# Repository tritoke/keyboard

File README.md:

# keyboard

This is my efforts towards making the exact keyboard entirely for fun.

Wants:
- Usable over USB or Bluetooth
- 65% with arrow keys, ISO enter and the four keys on the right

Progress:
- PCB (rev1 done)
- Case (freeCAD is kicking my ass)
- Firmware (I have some thoughts and that is all)

## PCB

Revision 1 of the PCB is now complete:

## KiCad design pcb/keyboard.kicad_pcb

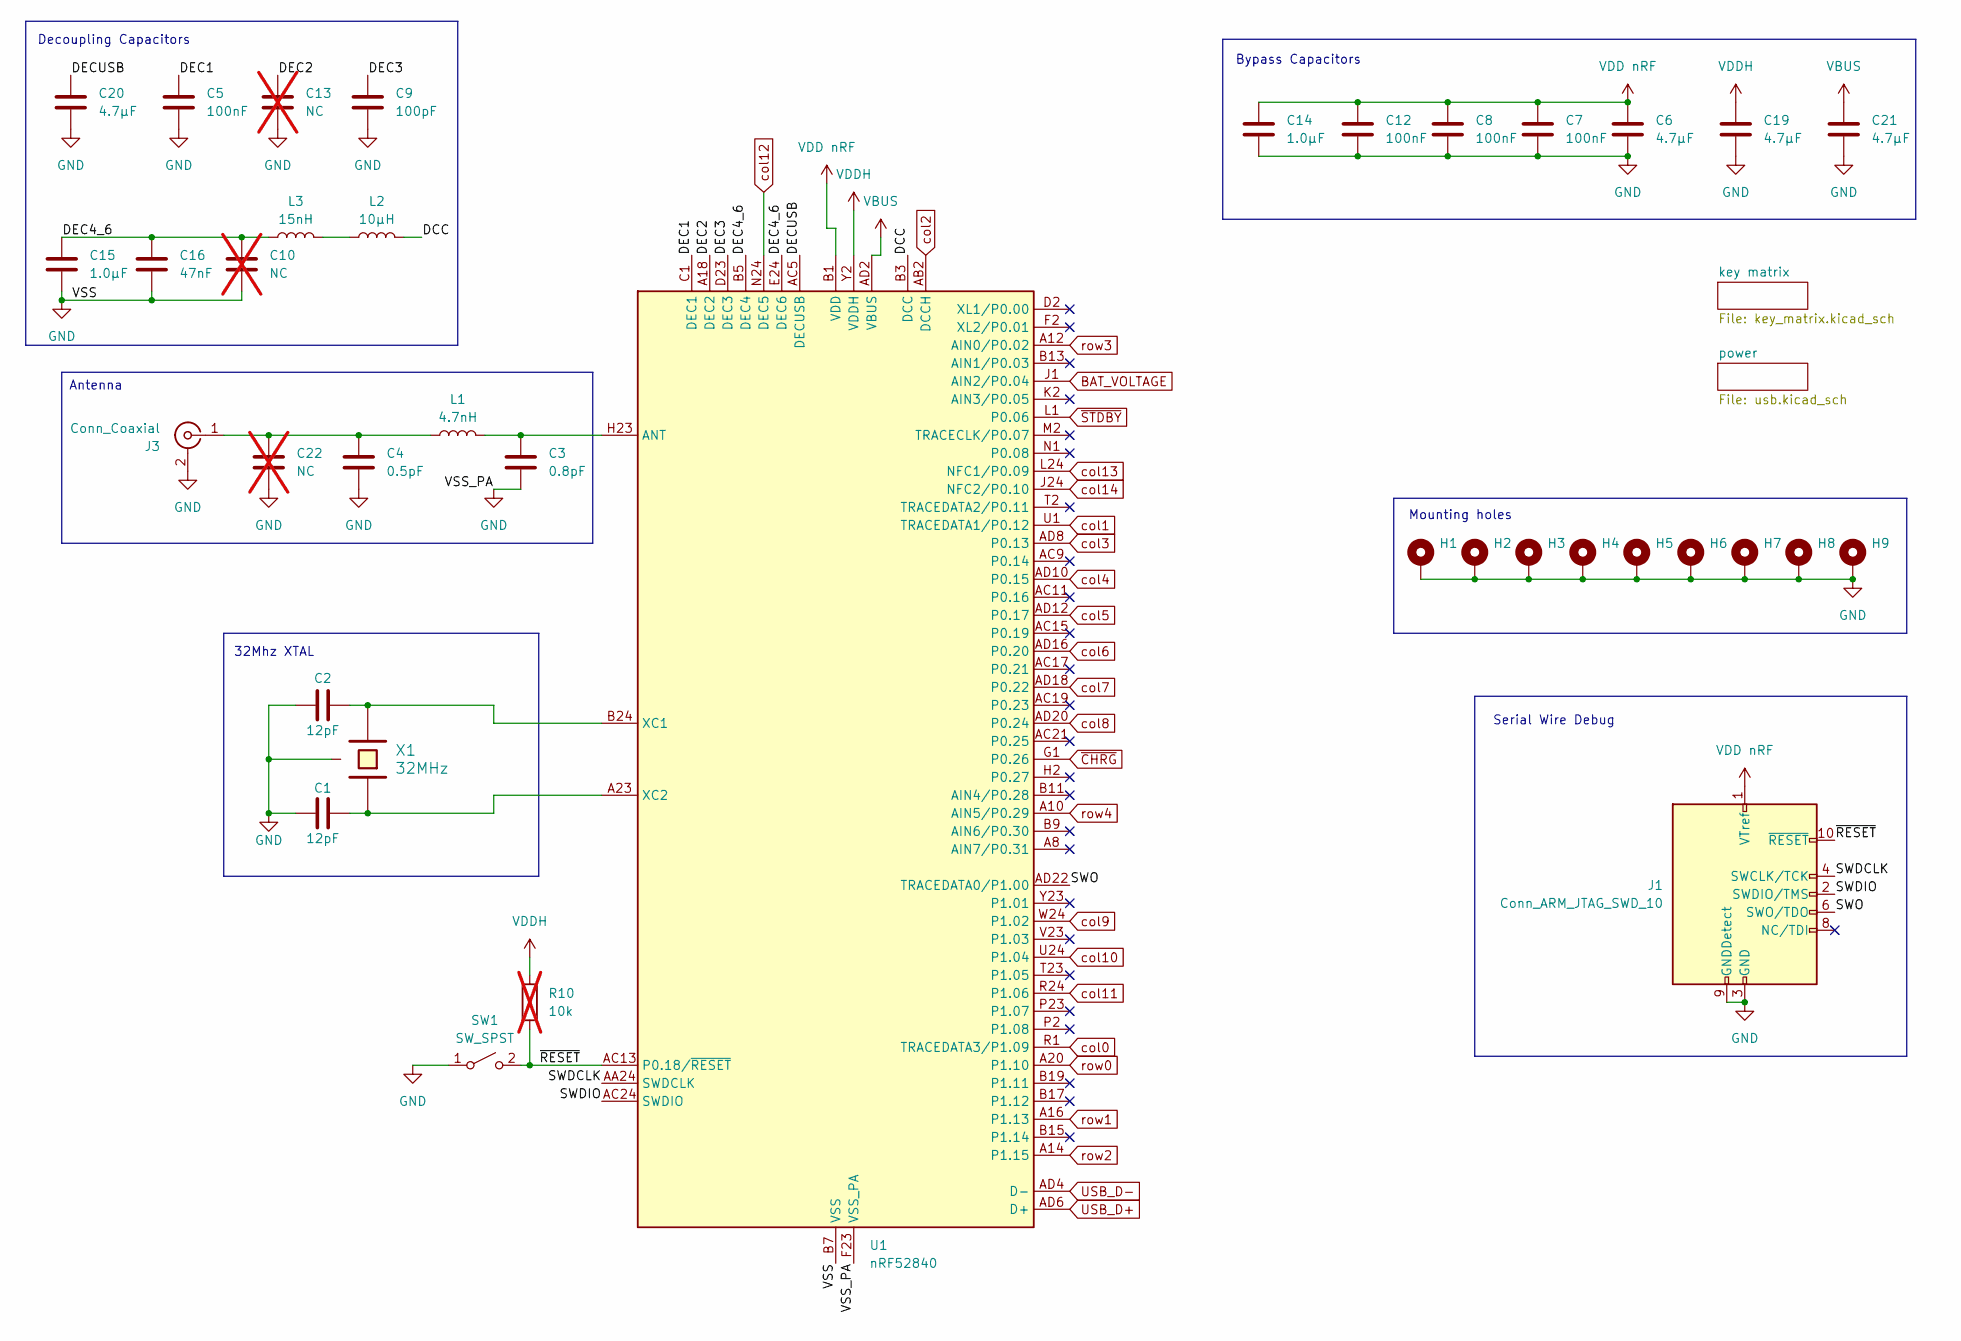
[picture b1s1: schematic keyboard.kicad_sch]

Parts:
C1, C2: 12pF; C_0603_1608Metric_Pad1.08x0.95mm_HandSolder
C3: 0.8pF; C_0603_1608Metric_Pad1.08x0.95mm_HandSolder
C4: 0.5pF; C_0603_1608Metric_Pad1.08x0.95mm_HandSolder
C5, C7, C8, C12: 100nF; C_0603_1608Metric_Pad1.08x0.95mm_HandSolder
C6, C19, C20, C21: 4.7µF; C_0603_1608Metric_Pad1.08x0.95mm_HandSolder
C9: 100pF; C_0603_1608Metric_Pad1.08x0.95mm_HandSolder
C10, C13, C22: NC; C_0603_1608Metric_Pad1.08x0.95mm_HandSolder; not fitted
C14, C15: 1.0µF; C_0603_1608Metric_Pad1.08x0.95mm_HandSolder
C16: 47nF; C_0603_1608Metric_Pad1.08x0.95mm_HandSolder
H1, H2, H3, H4, H5, H6, H7, H8, H9: MountingHole_Pad; MountingHole_2.2mm_M2_Pad_Via
J1: Conn_ARM_JTAG_SWD_10; IDC-Header_2x05_P2.54mm_Vertical
J3: Conn_Coaxial; SMA_Molex_73251-1153_EdgeMount_Horizontal_HandSolder
L1: 4.7nH; L_0603_1608Metric_Pad1.05x0.95mm_HandSolder
L2: 10µH; L_0603_1608Metric_Pad1.05x0.95mm_HandSolder
L3: 15nH; L_0603_1608Metric_Pad1.05x0.95mm_HandSolder
R10: 10k; R_0603_1608Metric_Pad0.98x0.95mm_HandSolder; not fitted
SW1: SW_SPST; Legion SS11
U1: nRF52840; Nordic_AQFN-73-1EP_7x7mm_P0.5mm
X1: 32MHz; Crystal_SMD_2016-4Pin_2.0x1.6mm_HandSolder

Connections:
/DCC: L2.2, U1.B3 (DCC)
/DEC1: C5.1, U1.C1 (DEC1)
/DEC2: C13.1, U1.A18 (DEC2)
/DEC3: C9.1, U1.D23 (DEC3)
/DEC4_6: C10.1, C15.1, C16.1, L3.1, U1.B5 (DEC4), U1.E24 (DEC6)
/DECUSB: C20.1, U1.AC5 (DECUSB)
/SWDCLK: J1.4 (SWCLK/TCK), U1.AA24 (SWDCLK)
/SWDIO: J1.2 (SWDIO/TMS), U1.AC24 (SWDIO)
/SWO: J1.6 (SWO/TDO), U1.AD22 (TRACEDATA0/P1.00)
/~RESET: J1.10 (~RESET), R10.2, SW1.2 (B), U1.AC13 (P0.18/~RESET)
BAT_VOLTAGE: U1.J1 (AIN2/P0.04); also elsewhere on the board
GND: C1.1, C2.1, C3.2, C4.2, C5.2, C6.2, C7.2, C8.2, C9.2, C10.2, C12.2, C13.2, C14.2, C15.2, C16.2, C19.2, C20.2, C21.2, C22.2, H1.1 (1_1), H2.1 (1_1), H3.1 (1_1), H4.1 (1_1), H5.1 (1_1), H6.1 (1_1), H7.1 (1_1), H8.1 (1_1), H9.1 (1_1), J1.3 (GND), J1.5 (GND), J1.9 (GNDDetect), J3.2 (Ext), SW1.1 (A), U1.B7 (VSS), U1.EP (VSS), U1.F23 (VSS_PA), X1.3; also elsewhere on the board
unnamed: C4.1, C22.1, J3.1 (In), L1.1
unnamed: L2.1, L3.2
unnamed: C3.1, L1.2, U1.H23 (ANT)
unnamed: C2.2, U1.B24 (XC1), X1.2
unnamed: C1.2, U1.A23 (XC2), X1.1
USB_D+: U1.AD6 (D+); also elsewhere on the board
USB_D-: U1.AD4 (D-); also elsewhere on the board
VBUS: C21.1, U1.AD2 (VBUS); also elsewhere on the board
VDD nRF: C6.1, C7.1, C8.1, C12.1, C14.1, J1.1 (VTref), U1.A22 (VDD), U1.AD14 (VDD), U1.AD23 (VDD), U1.B1 (VDD), U1.W1 (VDD)
VDDH: C19.1, R10.1, U1.Y2 (VDDH); also elsewhere on the board
col0: U1.R1 (TRACEDATA3/P1.09); also elsewhere on the board
col1: U1.U1 (TRACEDATA1/P0.12); also elsewhere on the board
col2: U1.AB2 (DCCH); also elsewhere on the board
col3: U1.AD8 (P0.13); also elsewhere on the board
col4: U1.AD10 (P0.15); also elsewhere on the board
col5: U1.AD12 (P0.17); also elsewhere on the board
col6: U1.AD16 (P0.20); also elsewhere on the board
col7: U1.AD18 (P0.22); also elsewhere on the board
col8: U1.AD20 (P0.24); also elsewhere on the board
col9: U1.W24 (P1.02); also elsewhere on the board
col10: U1.U24 (P1.04); also elsewhere on the board
col11: U1.R24 (P1.06); also elsewhere on the board
col12: U1.N24 (DEC5); also elsewhere on the board
col13: U1.L24 (NFC1/P0.09); also elsewhere on the board
col14: U1.J24 (NFC2/P0.10); also elsewhere on the board
row0: U1.A20 (P1.10); also elsewhere on the board
row1: U1.A16 (P1.13); also elsewhere on the board
row2: U1.A14 (P1.15); also elsewhere on the board
row3: U1.A12 (AIN0/P0.02); also elsewhere on the board
row4: U1.A10 (AIN5/P0.29); also elsewhere on the board
~CHRG: U1.G1 (P0.26); also elsewhere on the board
~STDBY: U1.L1 (P0.06); also elsewhere on the board

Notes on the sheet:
Bypass Capacitors
32Mhz XTAL
Mounting holes
Serial Wire Debug
Antenna
Decoupling Capacitors

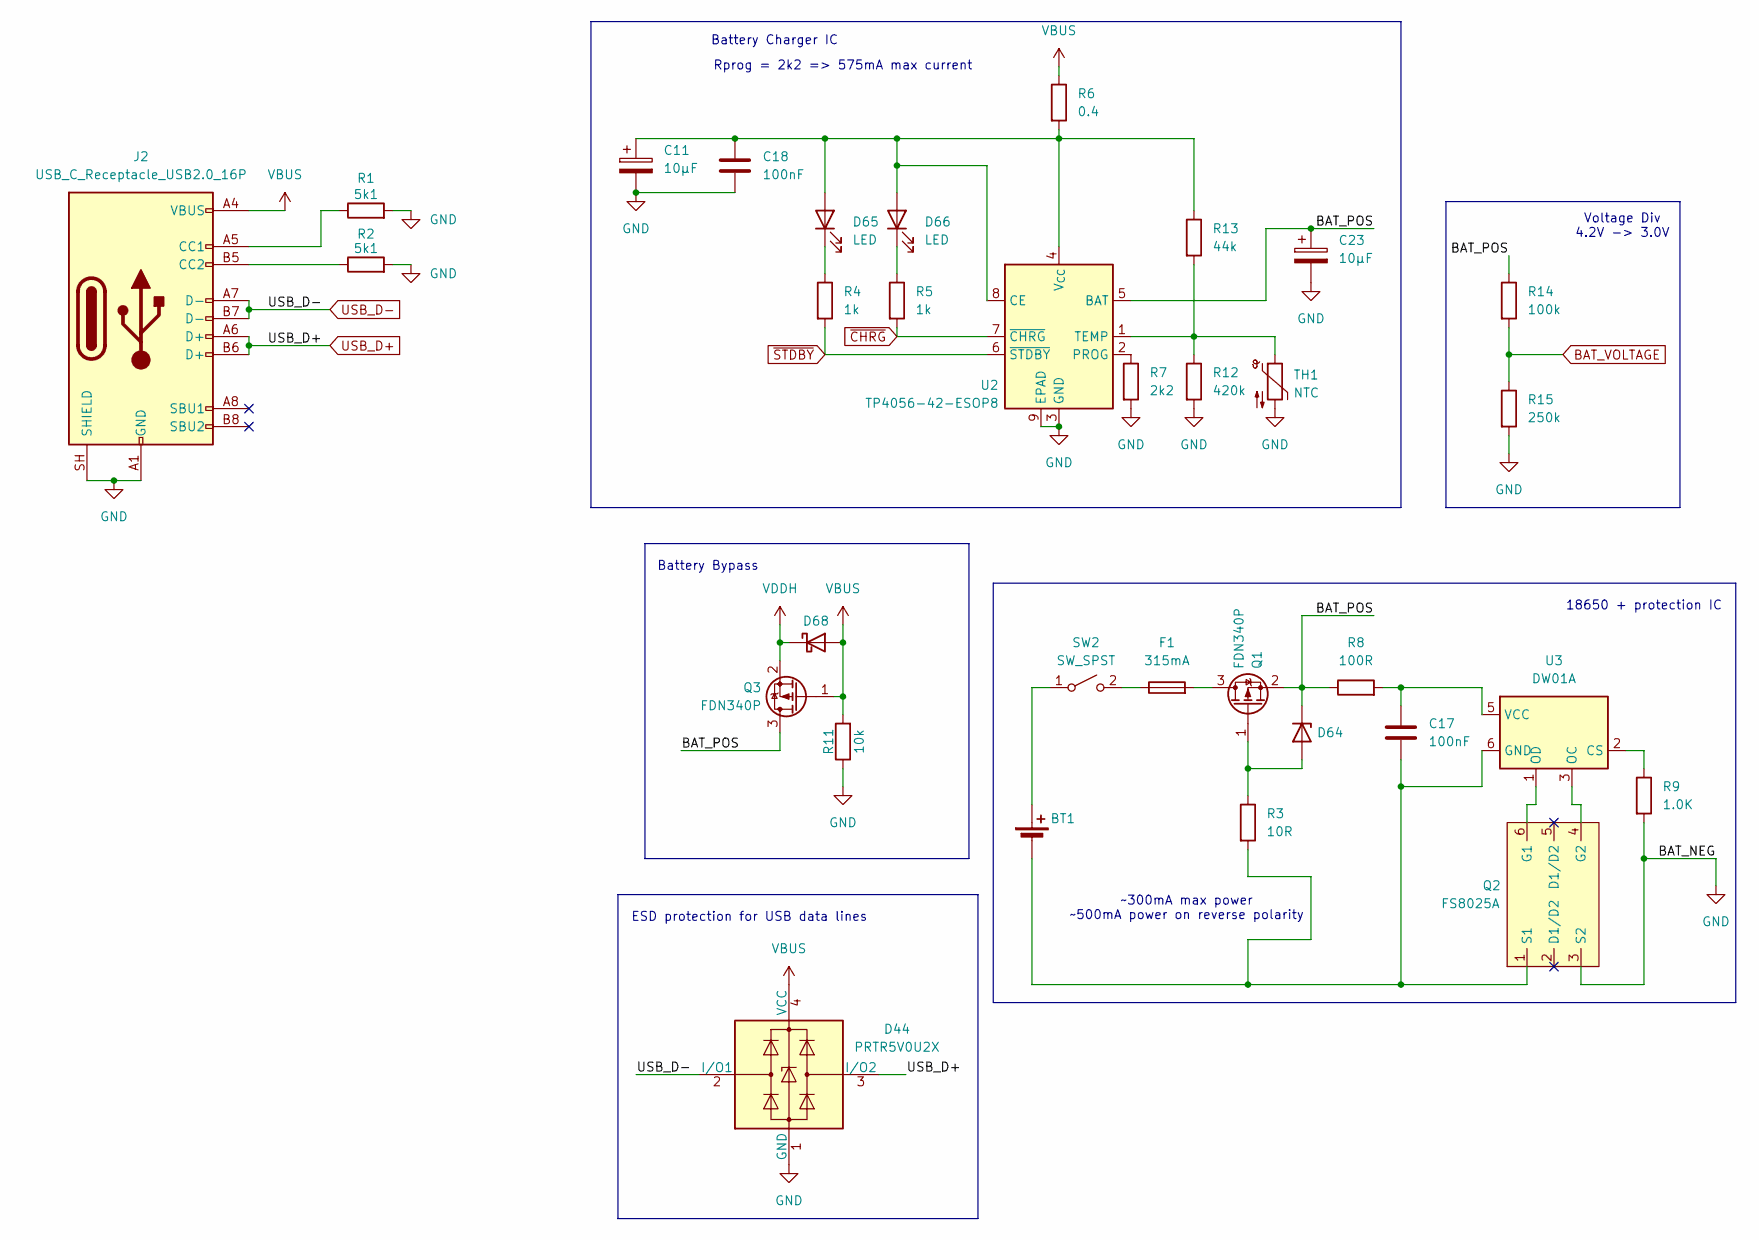
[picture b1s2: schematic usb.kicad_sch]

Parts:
BT1: Keystone 1042; BatteryHolder_Keystone_1042_1x18650
C11, C23: 10µF; CP_EIA-2012-15_AVX-P_HandSolder
C17, C18: 100nF; C_0603_1608Metric_Pad1.08x0.95mm_HandSolder
D44: PRTR5V0U2X; SOT-143
D64: 1SMB5918BT3G; D_SMB_Handsoldering
D65, D66: LED; LED_0603_1608Metric_Pad1.05x0.95mm_HandSolder
D68: MSS1P4-M3/89A; D_MicroSMP_LargeCathode
F1: 315mA; Fuse_0402_1005Metric_Pad0.77x0.64mm_HandSolder
J2: USB_C_Receptacle_USB2.0_16P; USB_C_Receptacle_G-Switch_GT-USB-7010ASV_handsolder_lmao.csv
Q1, Q3: FDN340P; SOT-23_Handsoldering
Q2: FS8025A; SOT-23-6_Handsoldering
R1, R2: 5k1; R_0805_2012Metric_Pad1.20x1.40mm_HandSolder
R3: 10R; R_0805_2012Metric_Pad1.20x1.40mm_HandSolder
R4, R5: 1k; R_0603_1608Metric_Pad0.98x0.95mm_HandSolder
R6: 0.4; R_0805_2012Metric_Pad1.20x1.40mm_HandSolder
R7: 2k2; R_0805_2012Metric_Pad1.20x1.40mm_HandSolder
R8: 100R; R_0805_2012Metric_Pad1.20x1.40mm_HandSolder
R9: 1.0K; R_0805_2012Metric_Pad1.20x1.40mm_HandSolder
R11: 10k; R_0805_2012Metric_Pad1.20x1.40mm_HandSolder
R12: 420k; R_0805_2012Metric_Pad1.20x1.40mm_HandSolder
R13: 44k; R_0805_2012Metric_Pad1.20x1.40mm_HandSolder
R14: 100k; R_0805_2012Metric_Pad1.20x1.40mm_HandSolder
R15: 250k; R_0805_2012Metric_Pad1.20x1.40mm_HandSolder
SW2: SW_SPST; Legion SS11
TH1: NTC; R_0805_2012Metric_Pad1.20x1.40mm_HandSolder
U2: TP4056-42-ESOP8; SOIC-8-1EP_3.9x4.9mm_P1.27mm_EP2.29x3mm
U3: DW01A; SOT-23-6

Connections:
/power/BAT_POS: C23.1, D64.1 (K), Q1.2 (S), Q3.3 (D), R8.1, R14.1, U2.5 (BAT)
BAT_VOLTAGE: R14.2, R15.1; also elsewhere on the board
GND: C11.2, C18.2, C23.2, D44.1 (GND), J2.A1 (GND), J2.A12 (GND), J2.B1 (GND), J2.B12 (GND), J2.SH (SHIELD), Q2.3 (S2), R1.2, R2.2, R7.2, R9.2, R11.1, R12.2, R15.2, TH1.2, U2.3 (GND), U2.9 (EPAD); also elsewhere on the board
unnamed: BT1.1 (+), SW2.1 (A)
unnamed: BT1.2 (-), C17.2, Q2.1 (S1), R3.2, U3.6 (GND)
unnamed: D64.2 (A), Q1.1 (G), R3.1
unnamed: C11.1, C18.1, D65.2 (A), D66.2 (A), R6.2, R13.1, U2.4 (V_{CC}), U2.8 (CE)
unnamed: D65.1 (K), R4.1
unnamed: D66.1 (K), R5.1
unnamed: J2.A5 (CC1), R1.1
unnamed: J2.B5 (CC2), R2.1
unnamed: F1.2, Q1.3 (D)
unnamed: Q2.6 (G1), U3.1 (OD)
unnamed: Q2.4 (G2), U3.3 (OC)
unnamed: F1.1, SW2.2 (B)
unnamed: R7.1, U2.2 (PROG)
unnamed: R12.1, R13.2, TH1.1, U2.1 (TEMP)
unnamed: R9.1, U3.2 (CS)
unnamed: C17.1, R8.2, U3.5 (VCC)
USB_D+: D44.3 (I/O2), J2.A6 (D+), J2.B6 (D+); also elsewhere on the board
USB_D-: D44.2 (I/O1), J2.A7 (D-), J2.B7 (D-); also elsewhere on the board
VBUS: D44.4 (VCC), D68.2 (A), J2.A4 (VBUS), J2.A9 (VBUS), J2.B4 (VBUS), J2.B9 (VBUS), Q3.1 (G), R6.1, R11.2; also elsewhere on the board
VDDH: D68.1 (K), Q3.2 (S); also elsewhere on the board
~CHRG: R5.2, U2.7 (~CHRG); also elsewhere on the board
~STDBY: R4.2, U2.6 (~STDBY); also elsewhere on the board

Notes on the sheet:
Voltage Div 4.2V -> 3.0V
Rprog = 2k2 => 575mA max current
18650 + protection IC
Battery Charger IC
ESD protection for USB data lines
~300mA max power ~500mA power on reverse polarity
Battery Bypass

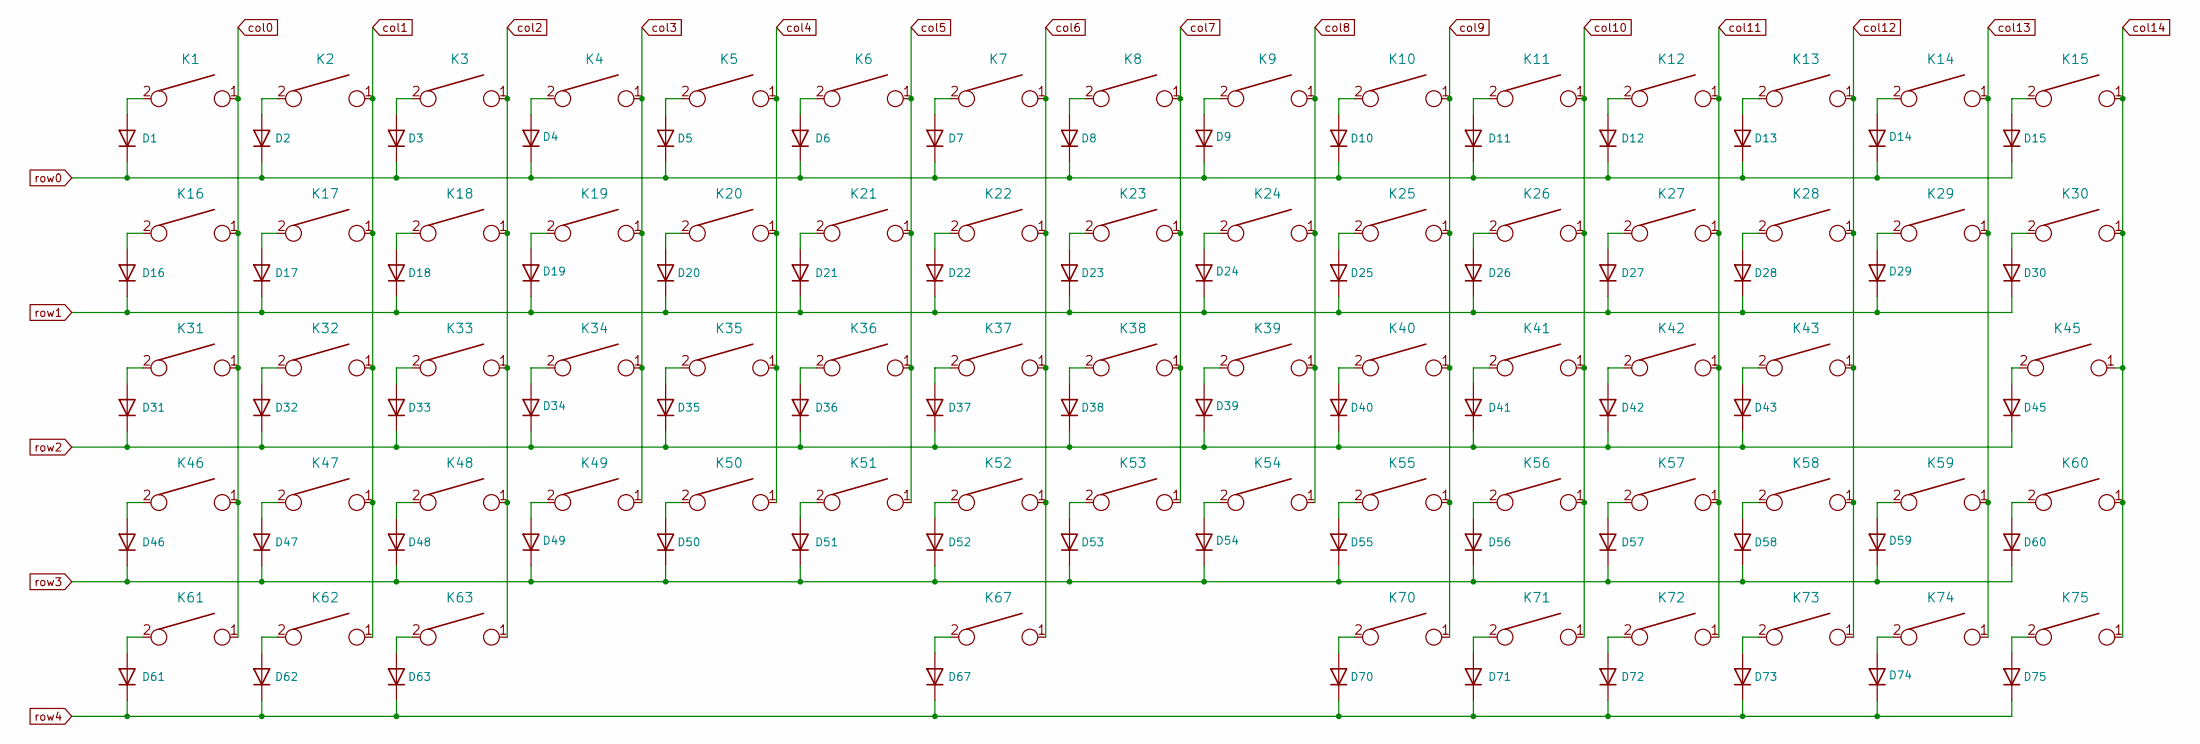
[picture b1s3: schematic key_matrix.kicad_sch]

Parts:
D1, D2, D3, D4, D5, D6, D7, D8, D9, D10, D11, D12, D13, D14, D15, D16, D17, D18, D19, D20, D21, D22, D23, D24, D25, D26, D27, D28, D29, D30, D31, D32, D33, D34, D35, D36, D37, D38, D39, D40, D41, D42, D43, D45, D46, D47, D48, D49, D50, D51, D52, D53, D54, D55, D56, D57, D58, D59, D60, D61, D62, D63, D67, D70, D71, D72, D73, D74, D75: D; D_0805_2012Metric_Pad1.15x1.40mm_HandSolder
K1, K2, K3, K4, K5, K6, K7, K8, K9, K10, K11, K12, K13, K15, K17, K18, K19, K20, K21, K22, K23, K24, K25, K26, K27, K28, K30, K32, K33, K34, K35, K36, K37, K38, K39, K40, K41, K42, K43, K45, K47, K48, K49, K50, K51, K52, K53, K54, K55, K56, K57, K59, K60, K70, K71, K72, K73, K74, K75: KEYSW; SW_Hotswap_Kailh_MX_1.00u
K14: KEYSW; SW_Hotswap_Kailh_MX_2.00u_Stabilised
K16, K46, K61, K62, K63: KEYSW; SW_Hotswap_Kailh_MX_1.25u
K29: KEYSW; SW_Hotswap_Kailh_MX_ISOEnter_Stabilised
K31, K58: KEYSW; SW_Hotswap_Kailh_MX_1.75u
K67: KEYSW; SW_Hotswap_Kailh_MX_6.25u_Stabilised

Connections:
unnamed: D1.2 (A), K1.2
unnamed: D2.2 (A), K2.2
unnamed: D3.2 (A), K3.2
unnamed: D4.2 (A), K4.2
unnamed: D5.2 (A), K5.2
unnamed: D6.2 (A), K6.2
unnamed: D7.2 (A), K7.2
unnamed: D8.2 (A), K8.2
unnamed: D9.2 (A), K9.2
unnamed: D10.2 (A), K10.2
unnamed: D11.2 (A), K11.2
unnamed: D12.2 (A), K12.2
unnamed: D13.2 (A), K13.2
unnamed: D14.2 (A), K14.2
unnamed: D15.2 (A), K15.2
unnamed: D16.2 (A), K16.2
unnamed: D17.2 (A), K17.2
unnamed: D18.2 (A), K18.2
unnamed: D19.2 (A), K19.2
unnamed: D20.2 (A), K20.2
unnamed: D21.2 (A), K21.2
unnamed: D22.2 (A), K22.2
unnamed: D23.2 (A), K23.2
unnamed: D24.2 (A), K24.2
unnamed: D25.2 (A), K25.2
unnamed: D26.2 (A), K26.2
unnamed: D27.2 (A), K27.2
unnamed: D28.2 (A), K28.2
unnamed: D29.2 (A), K29.2
unnamed: D30.2 (A), K30.2
unnamed: D31.2 (A), K31.2
unnamed: D32.2 (A), K32.2
unnamed: D33.2 (A), K33.2
unnamed: D34.2 (A), K34.2
unnamed: D35.2 (A), K35.2
unnamed: D36.2 (A), K36.2
unnamed: D37.2 (A), K37.2
unnamed: D38.2 (A), K38.2
unnamed: D39.2 (A), K39.2
unnamed: D40.2 (A), K40.2
unnamed: D41.2 (A), K41.2
unnamed: D42.2 (A), K42.2
unnamed: D43.2 (A), K43.2
unnamed: D45.2 (A), K45.2
unnamed: D46.2 (A), K46.2
unnamed: D47.2 (A), K47.2
unnamed: D48.2 (A), K48.2
unnamed: D49.2 (A), K49.2
unnamed: D50.2 (A), K50.2
unnamed: D51.2 (A), K51.2
unnamed: D52.2 (A), K52.2
unnamed: D53.2 (A), K53.2
unnamed: D54.2 (A), K54.2
unnamed: D55.2 (A), K55.2
unnamed: D56.2 (A), K56.2
unnamed: D57.2 (A), K57.2
unnamed: D58.2 (A), K58.2
unnamed: D59.2 (A), K59.2
unnamed: D60.2 (A), K60.2
unnamed: D61.2 (A), K61.2
unnamed: D62.2 (A), K62.2
unnamed: D63.2 (A), K63.2
unnamed: D67.2 (A), K67.2
unnamed: D70.2 (A), K70.2
unnamed: D71.2 (A), K71.2
unnamed: D72.2 (A), K72.2
unnamed: D73.2 (A), K73.2
unnamed: D74.2 (A), K74.2
unnamed: D75.2 (A), K75.2
col0: K1.1, K16.1, K31.1, K46.1, K61.1; also elsewhere on the board
col1: K2.1, K17.1, K32.1, K47.1, K62.1; also elsewhere on the board
col2: K3.1, K18.1, K33.1, K48.1, K63.1; also elsewhere on the board
col3: K4.1, K19.1, K34.1, K49.1; also elsewhere on the board
col4: K5.1, K20.1, K35.1, K50.1; also elsewhere on the board
col5: K6.1, K21.1, K36.1, K51.1; also elsewhere on the board
col6: K7.1, K22.1, K37.1, K52.1, K67.1; also elsewhere on the board
col7: K8.1, K23.1, K38.1, K53.1; also elsewhere on the board
col8: K9.1, K24.1, K39.1, K54.1; also elsewhere on the board
col9: K10.1, K25.1, K40.1, K55.1, K70.1; also elsewhere on the board
col10: K11.1, K26.1, K41.1, K56.1, K71.1; also elsewhere on the board
col11: K12.1, K27.1, K42.1, K57.1, K72.1; also elsewhere on the board
col12: K13.1, K28.1, K43.1, K58.1, K73.1; also elsewhere on the board
col13: K14.1, K29.1, K59.1, K74.1; also elsewhere on the board
col14: K15.1, K30.1, K45.1, K60.1, K75.1; also elsewhere on the board
row0: D1.1 (K), D2.1 (K), D3.1 (K), D4.1 (K), D5.1 (K), D6.1 (K), D7.1 (K), D8.1 (K), D9.1 (K), D10.1 (K), D11.1 (K), D12.1 (K), D13.1 (K), D14.1 (K), D15.1 (K); also elsewhere on the board
row1: D16.1 (K), D17.1 (K), D18.1 (K), D19.1 (K), D20.1 (K), D21.1 (K), D22.1 (K), D23.1 (K), D24.1 (K), D25.1 (K), D26.1 (K), D27.1 (K), D28.1 (K), D29.1 (K), D30.1 (K); also elsewhere on the board
row2: D31.1 (K), D32.1 (K), D33.1 (K), D34.1 (K), D35.1 (K), D36.1 (K), D37.1 (K), D38.1 (K), D39.1 (K), D40.1 (K), D41.1 (K), D42.1 (K), D43.1 (K), D45.1 (K); also elsewhere on the board
row3: D46.1 (K), D47.1 (K), D48.1 (K), D49.1 (K), D50.1 (K), D51.1 (K), D52.1 (K), D53.1 (K), D54.1 (K), D55.1 (K), D56.1 (K), D57.1 (K), D58.1 (K), D59.1 (K), D60.1 (K); also elsewhere on the board
row4: D61.1 (K), D62.1 (K), D63.1 (K), D67.1 (K), D70.1 (K), D71.1 (K), D72.1 (K), D73.1 (K), D74.1 (K), D75.1 (K); also elsewhere on the board

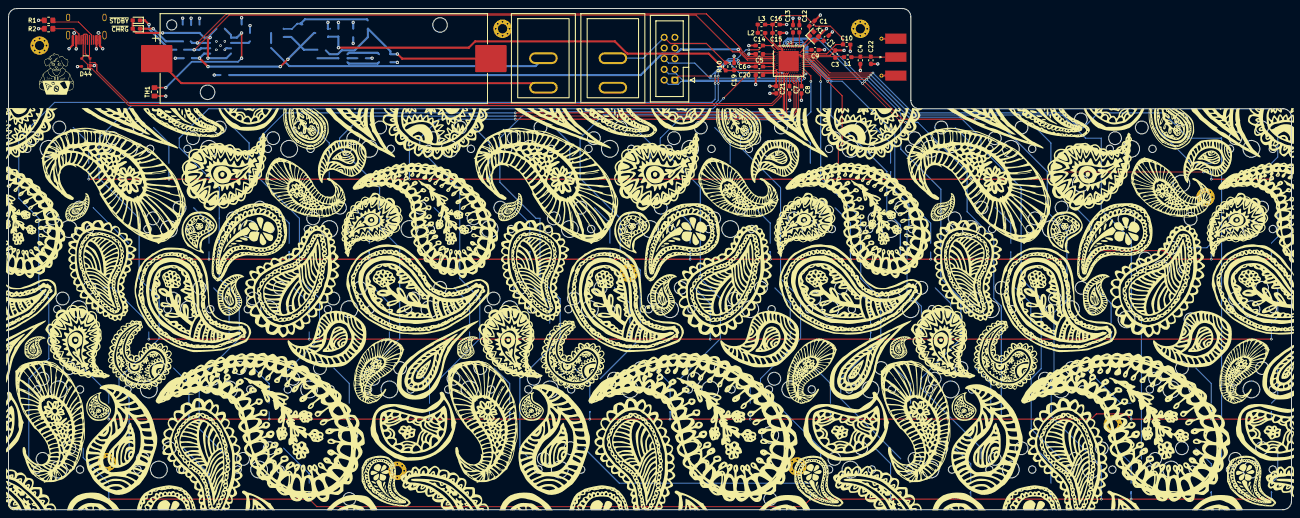
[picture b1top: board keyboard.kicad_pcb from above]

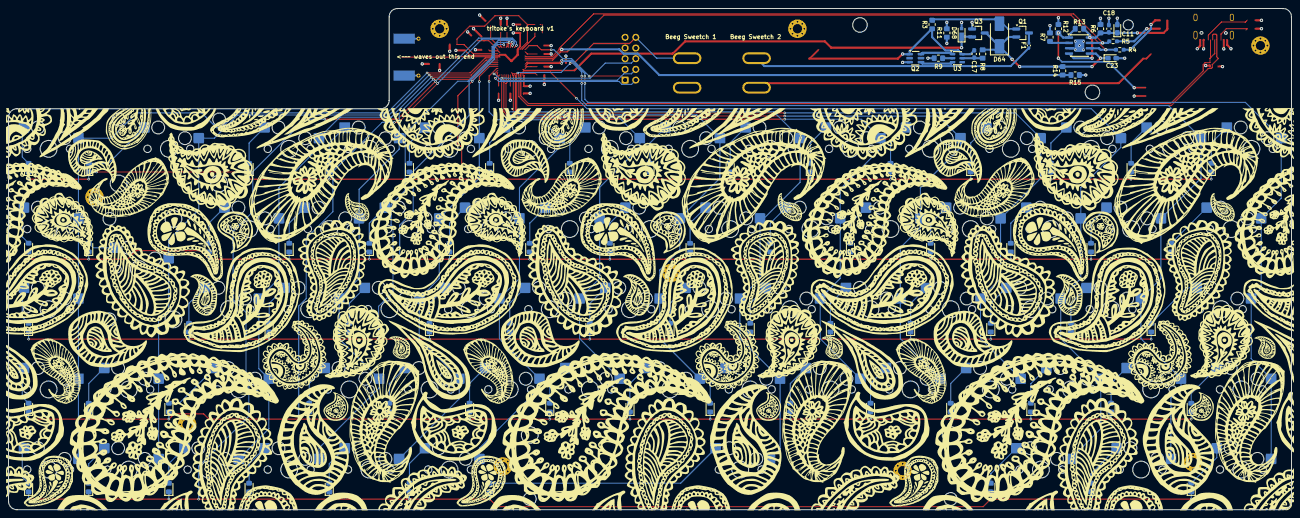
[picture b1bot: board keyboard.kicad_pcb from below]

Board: 4 copper layers, 304.8 x 119.1 mm, 208 parts (93 on the bottom side), 130 nets.

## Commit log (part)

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2026-02-02 Add datasheets as git LFS objects
2026-02-03 Add submodules for kicad footprints and schematics
2026-02-03 Change uc footprint over to aQFN to access USB pins
2026-02-09 Add case concept
2026-02-09 WIP: power / battery schematic
2026-02-10 WIP: power / battery schematic 2
2026-02-11 First version of power circuitry complete?
2026-02-12 Add an on/off switch
2026-02-12 Start assigning footprints
2026-02-13 Fix MOSFET orientation
2026-02-13 Fix and complete keyswitch assignments
2026-02-18 Add battery protection IC
2026-02-25 Finish power circuitry
2026-03-22 Fill in some more components
2026-03-22 Pick a battery and add extra parts for TP4056
2026-04-13 Update to kicad 10
2026-04-14 Add a stabilised footprint for a 6.25u key
2026-04-15 Add remaining stabilised keys
2026-04-15 AHH THE TRAIN IS GETTING IN
2026-04-29 Place all keys
2026-04-30 Fix some labels
2026-04-30 Add notes from chat
2026-05-01 tinkering >:3
2026-06-16 Place all key matrix diodes
2026-06-16 Pick an NTC and calculate R1/R2
2026-06-18 Add USB-C link
2026-06-18 idk, moved some bits round?
2026-06-24 Did a bunch of stuff lol
2026-06-26 Fixed switch footprint
2026-06-26 Did some stuff
2026-06-29 Fix diode placement
2026-06-29 Did a bunch of things!
